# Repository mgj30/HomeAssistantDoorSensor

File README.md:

HomeAssistant Door Sensor : MQTTSimpleDoorSensor

Descripción
===========

Dispositivo Open Source, compatible con Home Assistant.

El dispositivo se basa en el encapsulado ESP8266, concretamente en la placa de
desarrollo WEMOS D1 mini.

Se trata de un dispositivo detector de apertura y cierre de puerta, por MQTT,
compatible con Home Assistant en adelante HA.

El dispositivo implementa el protocolo MQTT con auto Discovery de HA, y
proporciona una interfaz grafica de configuración parecida a TASMOTA.

Funcionamiento
==============

Una vez instalado el Firmware y montado la PCB siguiendo el esquemático, el
funcionamiento del dispositivo es el siguiente.

*Puesta en marcha*

En caso de no estar configurado, el dispositivo iniciará su Wifi como AP con el
SSID “SimpleDoorSensor” y contraseña “SimpleDoorSensor”, proporcionando en la
URL <http://192.168.1.1> , una interfaz de configuración, en la cual nos
encontraremos las siguientes opciones:

WIFI Configuration
------------------

En esta sección dispondremos de un formulario en el que podremos introducir, el
SSID y contraseña de la Red WIFI donde el dispositivo tendrá acceso al servidor
MQTT de nuestro HA.

En el formulario encontraremos los siguientes campos:

**SSID1:** SSID de la Red Wifi principal

**PWD1:** Contraseña de la Red Wifi principal

**SSID2:** SSID de la Red Wifi secundaria

**PWD2:** Contraseña de la Red Wifi secundaria

MQTT Configuration
------------------

En esta sección disponemos de un formulario con los siguientes campos, para
poder configurar un servidor MQTT en el que publicar datos.

En el formulario encontraremos los siguientes campos:

**SERVER:** IP o dominio del servidor MQTT

**PORT:** Puerto MQTT

**USER:** Usuario de autenticación

**PWD:** Contraseña de autenticación

**CLIENTID:** Identificación del cliente MQTT

Device Configuration
--------------------

En esta sección encontraremos un formulario con configuraciones generales del
sistema con los siguientes campos:

**HA_AUTODISCOVER:** Activa o desactiva el modo autodiscover

**DV_LEDS_STATUS:** Activa o desactiva encender los led de la PCB al leer la
batería

**DV_DEEPSLEEPTIME:** Por defecto -1(inhabilita dormir), 0 Duerme hasta abrir
puerta, +0 Despierta cada X segundos y publica estado.

**HA_DEVICENAME:** Nombre del dispositivo en HA

**DV_STATUS_PUBLISH_PERIOD:** Periodo de publicación en el caso de DeepSleeTime
= -1, por defecto 5 segundos

En la carpeta “Schematics” encontrareis el proyecto KiCad de la PCB junto con el
esquemático del circuito.

Por otro lado en la carpeta SRC se encuentra el código fuente del proyecto.

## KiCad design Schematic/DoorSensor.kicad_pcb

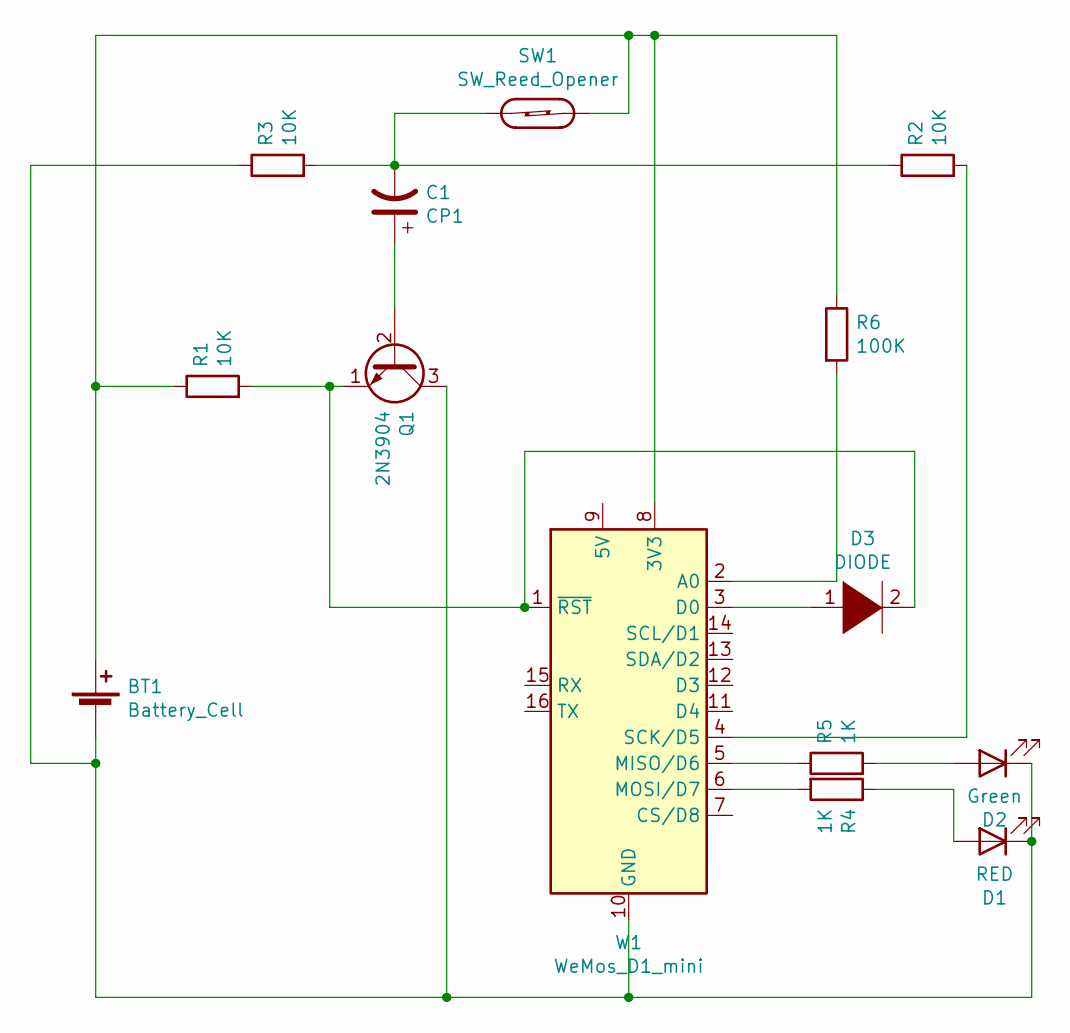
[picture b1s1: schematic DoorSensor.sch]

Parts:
BT1: Battery_Cell; BatteryHolder_Keystone_1042_1x18650
C1: CP1; CP_Radial_D4.0mm_P1.50mm
D1: RED; LED_D3.0mm
D2: Green; LED_D3.0mm
D3: DIODE; D_A-405_P7.62mm_Horizontal
Q1: 2N3904; TO-92_Inline
R1, R2, R3: 10K; R_Axial_DIN0309_L9.0mm_D3.2mm_P12.70mm_Horizontal
R4, R5: 1K; R_Axial_DIN0309_L9.0mm_D3.2mm_P12.70mm_Horizontal
R6: 100K; R_Axial_DIN0309_L9.0mm_D3.2mm_P12.70mm_Horizontal
SW1: SW_Reed_Opener; THT_reed_switch_20mmL
W1: WeMos_D1_mini; WEMOS_D1_mini_light

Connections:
unnamed: BT1.1 (+), R1.1, R6.1, SW1.2, W1.8 (3V3)
unnamed: BT1.2 (-), D1.1 (K), D2.1 (K), Q1.3 (C), R3.1, W1.10 (GND)
unnamed: C1.1, Q1.2 (B)
unnamed: C1.2, R2.1, R3.2, SW1.1
unnamed: D1.2 (A), R4.1
unnamed: D2.2 (A), R5.2
unnamed: D3.1 (K), W1.3 (D0)
unnamed: D3.2 (A), Q1.1 (E), R1.2, W1.1 (~RST)
unnamed: R2.2, W1.4 (SCK/D5)
unnamed: R4.2, W1.6 (MOSI/D7)
unnamed: R5.1, W1.5 (MISO/D6)
unnamed: R6.2, W1.2 (A0)

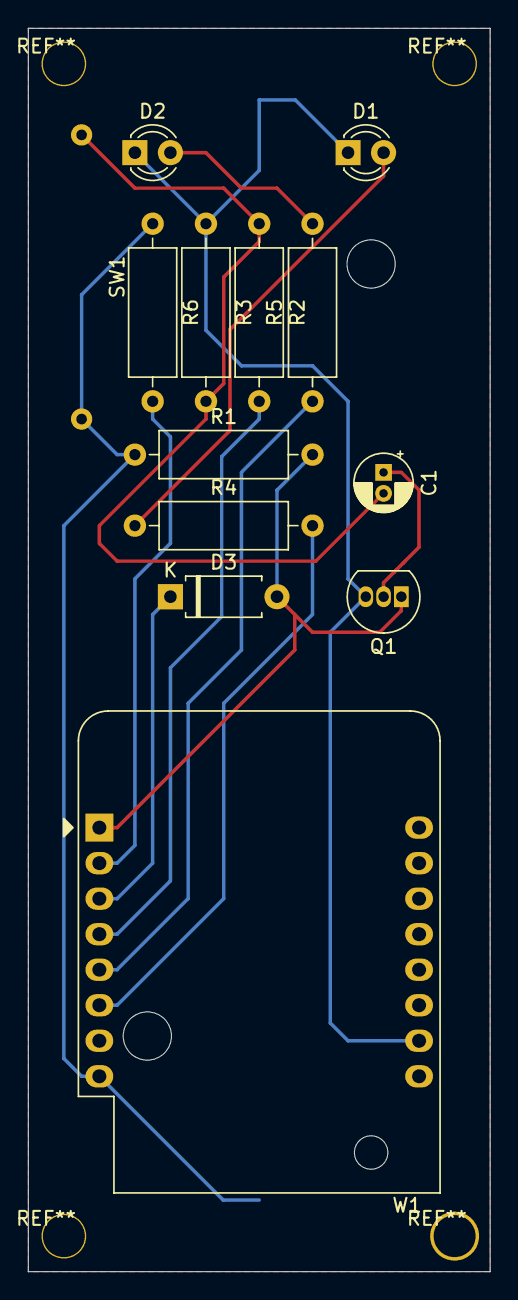
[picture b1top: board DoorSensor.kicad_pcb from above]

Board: 2 copper layers, 33.0 x 88.9 mm, 14 parts (1 on the bottom side), 12 nets.
